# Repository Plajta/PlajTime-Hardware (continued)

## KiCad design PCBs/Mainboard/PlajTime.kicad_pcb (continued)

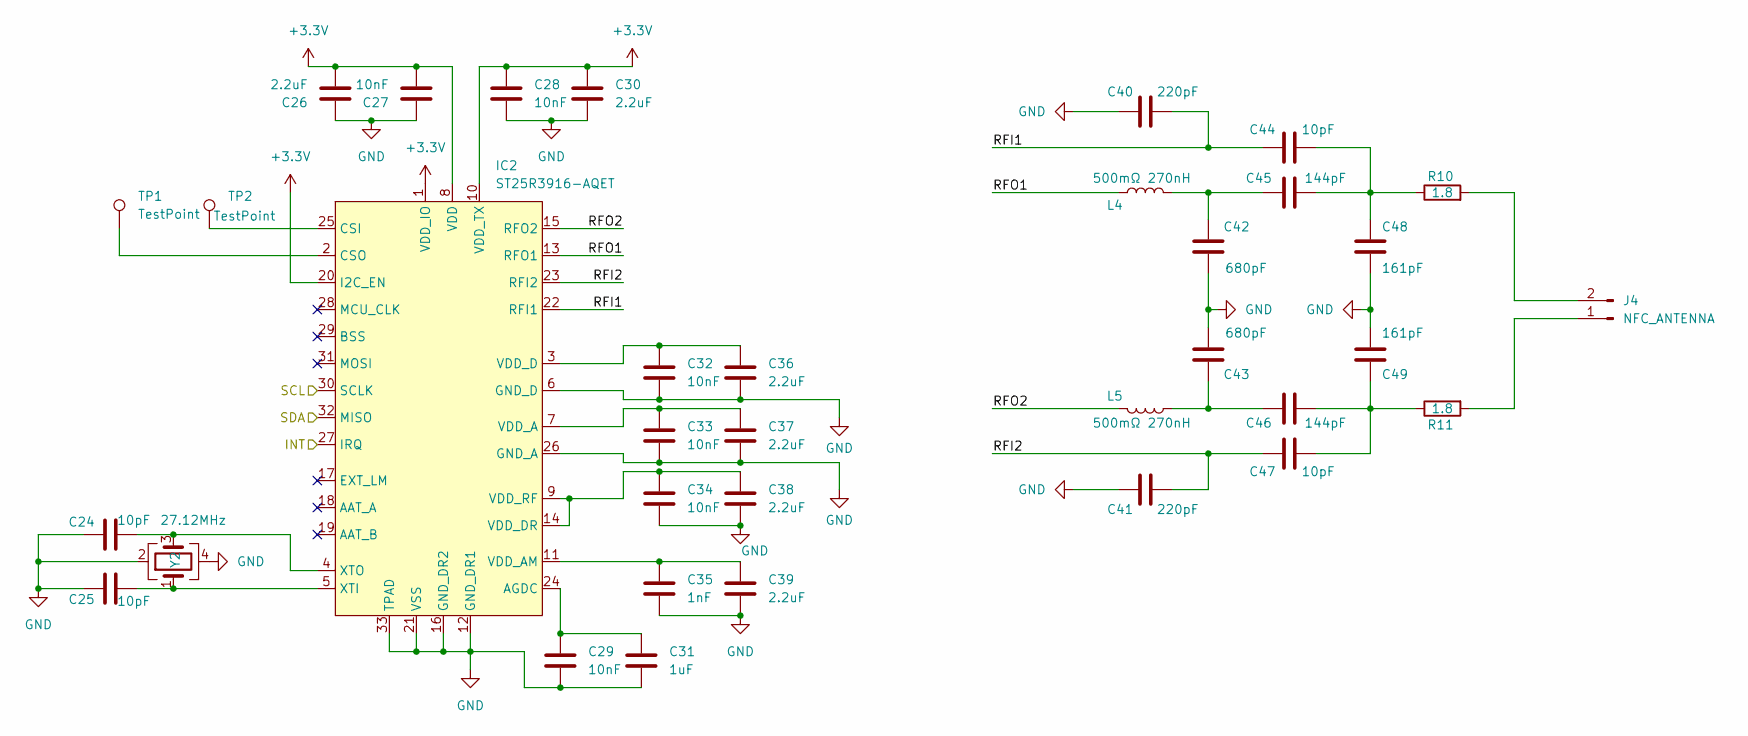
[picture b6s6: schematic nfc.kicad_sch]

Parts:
C24, C25, C44, C47: 10pF; C_0201_0603Metric
C26, C30, C36, C37, C38, C39: 2.2uF; C_0201_0603Metric
C27, C28, C29, C32, C33, C34: 10nF; C_0201_0603Metric
C31: 1uF; C_0201_0603Metric
C35: 1nF; C_0201_0603Metric
C40, C41: 220pF; C_0201_0603Metric
C42, C43: 680pF; C_0201_0603Metric
C45, C46: 144pF; C_0201_0603Metric
C48, C49: 161pF; C_0201_0603Metric
IC2: ST25R3916-AQET
J4: NFC_ANTENNA; PinHeader_1x02_P1.00mm_Vertical
L4, L5: 500mΩ 270nH; L_0603_1608Metric
R10, R11: 1.8; R_0201_0603Metric
TP1, TP2: TestPoint; TestPoint_Pad_D1.0mm
Y2: 27.12MHz; Oscillator_SMD_Abracon_ASCO-4Pin_1.6x1.2mm

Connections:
+3.3V: C26.2, C27.2, C28.1, C30.1, IC2.1 (VDD_IO), IC2.8 (VDD), IC2.10 (VDD_TX), IC2.20 (I2C_EN); also elsewhere on the board
/Display/SCL: IC2.30 (SCLK); also elsewhere on the board
/Display/SDA: IC2.32 (MISO); also elsewhere on the board
/NFC/RFI1: C40.2, C44.1, IC2.22 (RFI1)
/NFC/RFI2: C41.2, C47.1, IC2.23 (RFI2)
/NFC/RFO1: IC2.13 (RFO1), L4.1
/NFC/RFO2: IC2.15 (RFO2), L5.1
/NFC_INT: IC2.27 (IRQ); also elsewhere on the board
GND: C24.1, C25.2, C26.1, C27.1, C28.2, C29.2, C30.2, C31.2, C32.2, C33.2, C34.2, C35.2, C36.2, C37.2, C38.2, C39.2, C40.1, C41.1, C42.2, C43.2, C48.2, C49.2, IC2.6 (GND_D), IC2.12 (GND_DR1), IC2.16 (GND_DR2), IC2.21 (VSS), IC2.26 (GND_A), IC2.33 (TPAD), Y2.2, Y2.4; also elsewhere on the board
unnamed: C42.1, C45.1, L4.2
unnamed: C43.1, C46.1, L5.2
unnamed: C44.2, C45.2, C48.1, R10.1
unnamed: C46.2, C47.2, C49.1, R11.1
unnamed: C29.1, C31.1, IC2.24 (AGDC)
unnamed: IC2.25 (CSI), TP2.1
unnamed: IC2.2 (CSO), TP1.1
unnamed: C33.1, C37.1, IC2.7 (VDD_A)
unnamed: C35.1, C39.1, IC2.11 (VDD_AM)
unnamed: C32.1, C36.1, IC2.3 (VDD_D)
unnamed: C34.1, C38.1, IC2.9 (VDD_RF), IC2.14 (VDD_DR)
unnamed: C25.1, IC2.5 (XTI), Y2.1
unnamed: C24.2, IC2.4 (XTO), Y2.3
unnamed: J4.1, R11.2
unnamed: J4.2, R10.2

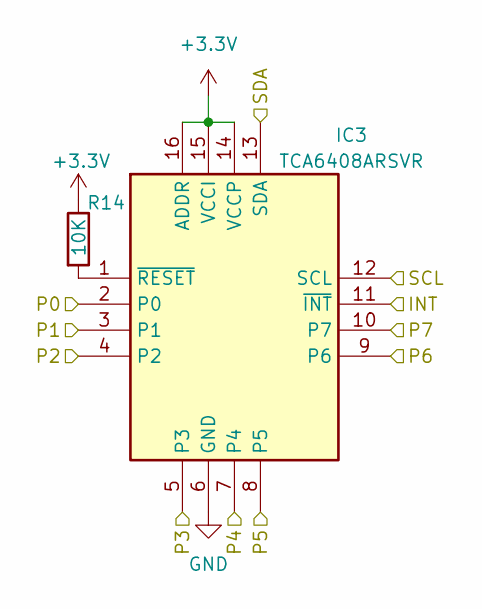
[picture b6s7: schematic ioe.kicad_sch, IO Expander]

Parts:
IC3: TCA6408ARSVR; QFN40P180X260X55-16N; Mouser Part Number 595-TCA6408ARSVR
R14: 10K; R_0201_0603Metric

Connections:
+3.3V: IC3.14 (VCCP), IC3.15 (VCCI), IC3.16 (ADDR), R14.1; also elsewhere on the board
/1V8_EN: IC3.5 (P3); also elsewhere on the board
/DP_RES: IC3.3 (P1); also elsewhere on the board
/Display/SCL: IC3.12 (SCL); also elsewhere on the board
/Display/SDA: IC3.13 (SDA); also elsewhere on the board
/ESP32_C3/INT2: IC3.11 (~INT); also elsewhere on the board
/IMU_INT: IC3.2 (P0); also elsewhere on the board
/LVL_SHIFT_EN: IC3.8 (P5); also elsewhere on the board
/NFC_INT: IC3.4 (P2); also elsewhere on the board
/OXY_INT: IC3.7 (P4); also elsewhere on the board
/PIC_INT: IC3.10 (P7); also elsewhere on the board
/VIC_INT: IC3.9 (P6); also elsewhere on the board
GND: IC3.6 (GND); also elsewhere on the board
unnamed: IC3.1 (~RESET), R14.2

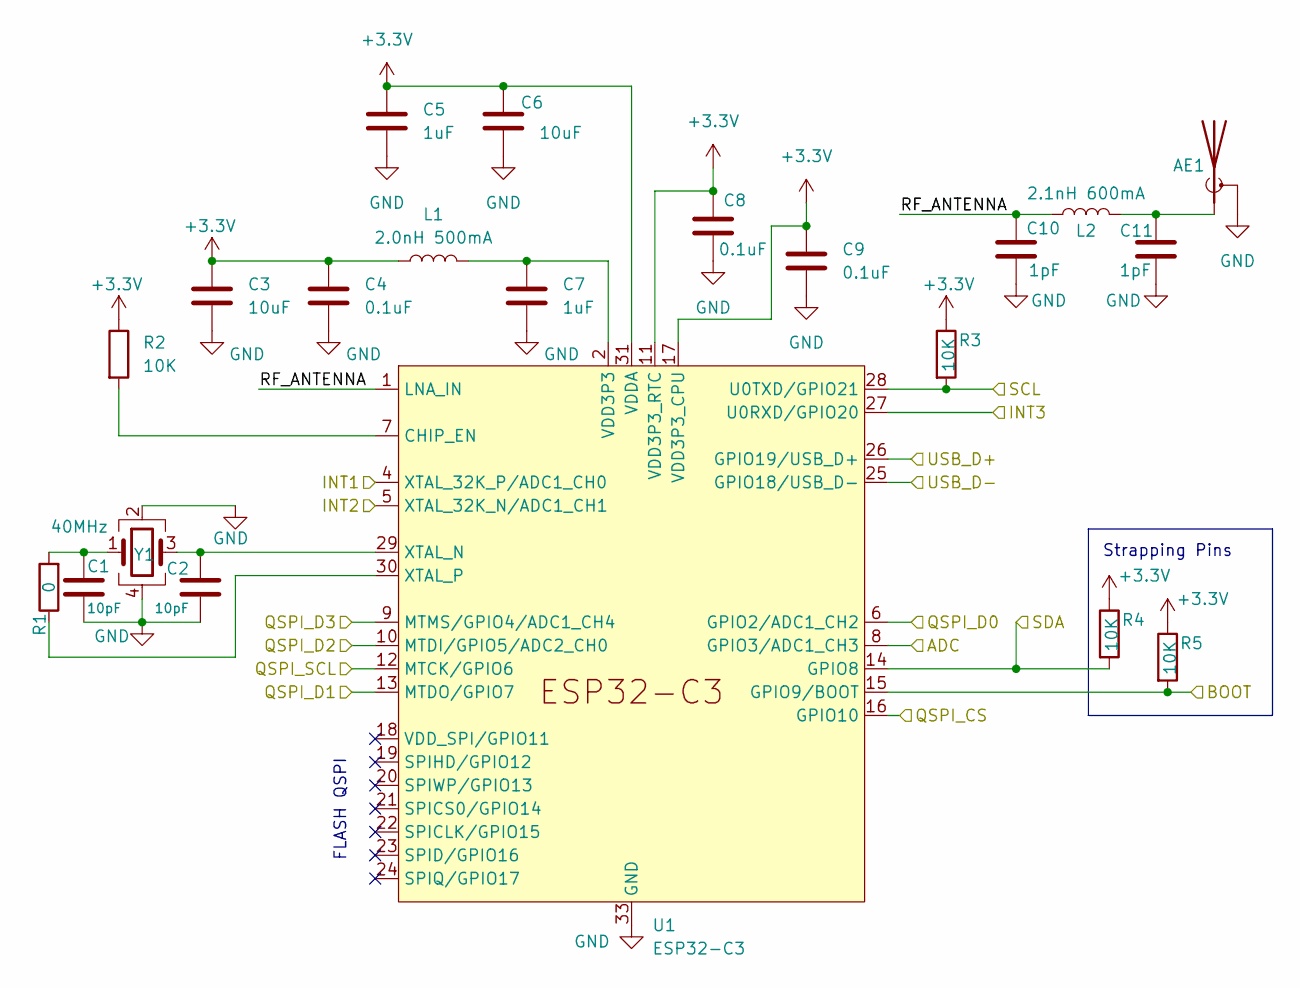
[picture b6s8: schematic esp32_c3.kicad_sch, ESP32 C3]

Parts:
AE1: Antenna_Shield; PinHeader_1x02_P1.00mm_Vertical
C1, C2: 10pF; C_0201_0603Metric
C3, C6: 10uF; C_0402_1005Metric
C4, C8, C9: 0.1uF; C_0201_0603Metric
C5, C7: 1uF; C_0201_0603Metric
C10, C11: 1pF; C_0201_0603Metric
L1: 2.0nH 500mA; L_0201_0603Metric
L2: 2.1nH 600mA; L_0201_0603Metric
R1: 0; R_0201_0603Metric
R2, R3, R4, R5: 10K; R_0201_0603Metric
U1: ESP32-C3; QFN-32-1EP_5x5mm_P0.5mm_EP3.45x3.45mm
Y1: 40MHz; Oscillator_SMD_Abracon_ASCO-4Pin_1.6x1.2mm

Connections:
+3.3V: C3.1, C4.1, C5.1, C6.1, C8.1, C9.1, L1.1, R2.1, R3.1, R4.1, R5.1, U1.11 (VDD3P3_RTC), U1.17 (VDD3P3_CPU), U1.31 (VDDA), U1.32 (VDDA); also elsewhere on the board
/Display/QSPI_CS: U1.16 (GPIO10); also elsewhere on the board
/Display/QSPI_D0: U1.6 (GPIO2/ADC1_CH2); also elsewhere on the board
/Display/QSPI_D1: U1.13 (MTDO/GPIO7); also elsewhere on the board
/Display/QSPI_D2: U1.10 (MTDI/GPIO5/ADC2_CH0); also elsewhere on the board
/Display/QSPI_D3: U1.9 (MTMS/GPIO4/ADC1_CH4); also elsewhere on the board
/Display/QSPI_SCL: U1.12 (MTCK/GPIO6); also elsewhere on the board
/Display/SCL: R3.2, U1.28 (U0TXD/GPIO21); also elsewhere on the board
/Display/SDA: R4.2, U1.14 (GPIO8); also elsewhere on the board
/Display/TE: U1.27 (U0RXD/GPIO20); also elsewhere on the board
/Display/TP_INT: U1.4 (XTAL_32K_P/ADC1_CH0); also elsewhere on the board
/ESP32_C3/ADC: U1.8 (GPIO3/ADC1_CH3); also elsewhere on the board
/ESP32_C3/BOOT: R5.2, U1.15 (GPIO9/BOOT); also elsewhere on the board
/ESP32_C3/INT2: U1.5 (XTAL_32K_N/ADC1_CH1); also elsewhere on the board
/ESP32_C3/RF_ANTENNA: C10.1, L2.1, U1.1 (LNA_IN)
/ESP32_C3/USB_D+: U1.26 (GPIO19/USB_D+); also elsewhere on the board
/ESP32_C3/USB_D-: U1.25 (GPIO18/USB_D-); also elsewhere on the board
GND: AE1.2 (Shield), C1.2, C2.2, C3.2, C4.2, C5.2, C6.2, C7.2, C8.2, C9.2, C10.2, C11.2, U1.33 (GND), Y1.2, Y1.4; also elsewhere on the board
unnamed: AE1.1 (A), C11.1, L2.2
unnamed: C1.1, R1.2, Y1.1
unnamed: C7.1, L1.2, U1.2 (VDD3P3), U1.3 (VDD3P3)
unnamed: R2.2, U1.7 (CHIP_EN)
unnamed: C2.1, U1.29 (XTAL_N), Y1.3
unnamed: R1.1, U1.30 (XTAL_P)

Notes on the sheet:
Strapping Pins
FLASH QSPI

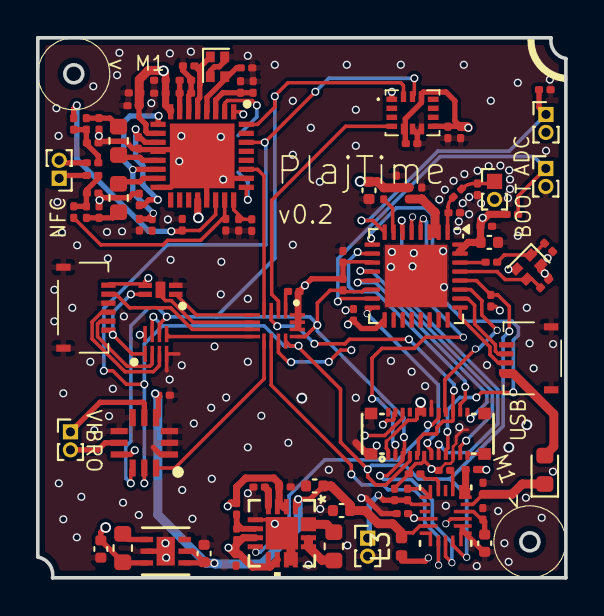
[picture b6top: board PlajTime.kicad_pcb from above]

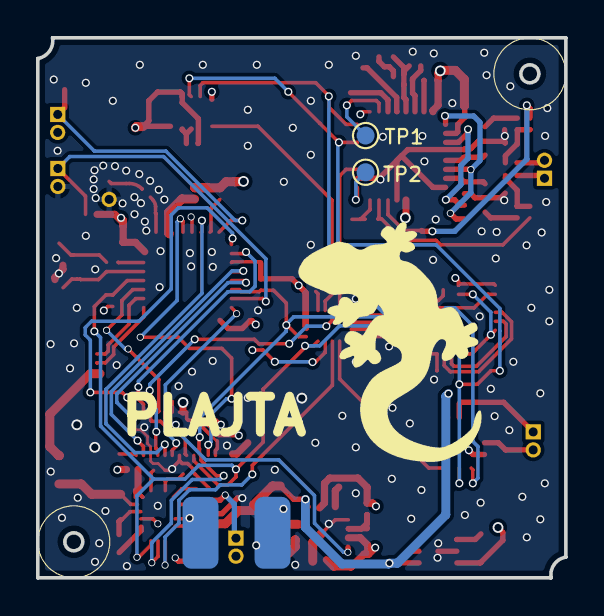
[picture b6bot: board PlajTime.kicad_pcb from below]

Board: 4 copper layers, 29.3 x 30.0 mm, 100 parts (3 on the bottom side), 76 nets.

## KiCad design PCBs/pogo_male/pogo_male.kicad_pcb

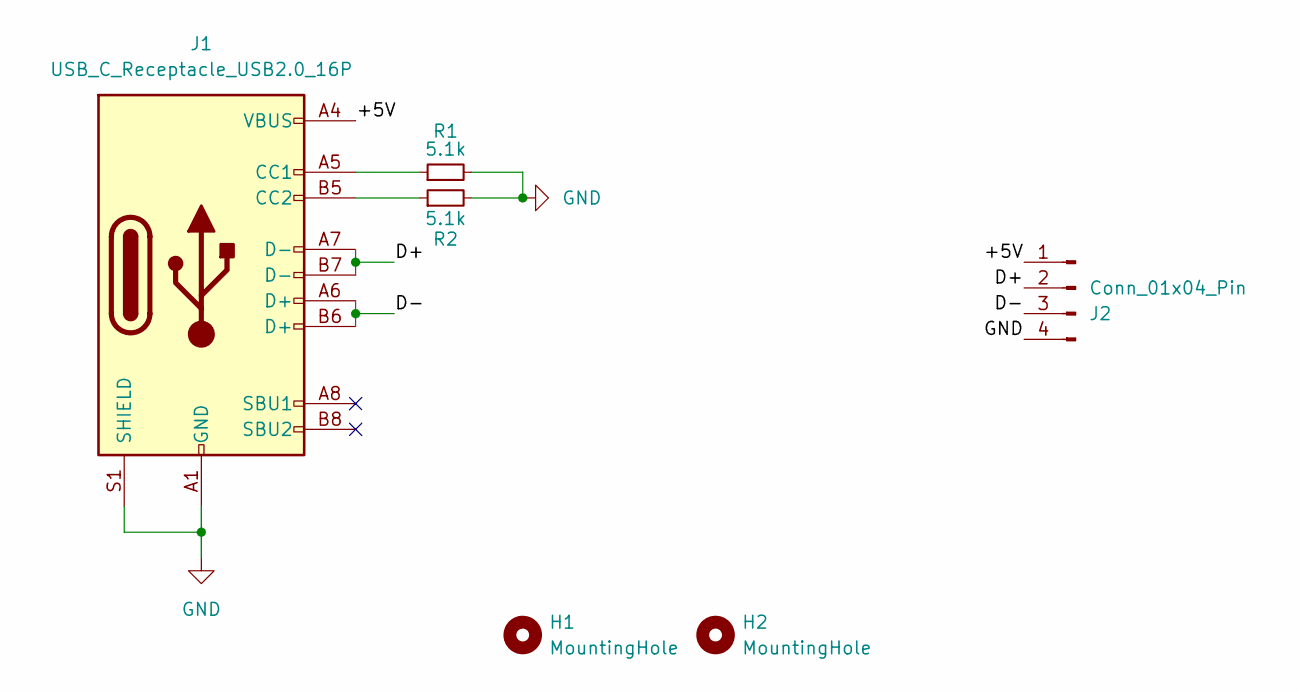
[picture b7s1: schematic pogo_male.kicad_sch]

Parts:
H1, H2: MountingHole; MountingHole_1.2mm_M1
J1: USB_C_Receptacle_USB2.0_16P; USB_C_Receptacle_G-Switch_GT-USB-7010ASV
J2: Conn_01x04_Pin; PinHeader_1x04_P2.54mm_Vertical
R1, R2: 5.1k; R_0402_1005Metric

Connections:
/+5V: J1.A4 (VBUS), J1.A9 (VBUS), J1.B4 (VBUS), J1.B9 (VBUS), J2.1
/D+: J1.A7 (D-), J1.B7 (D-), J2.2
/D-: J1.A6 (D+), J1.B6 (D+), J2.3
GND: J1.A1 (GND), J1.A12 (GND), J1.B1 (GND), J1.B12 (GND), J1.S1 (SHIELD), J2.4, R1.2, R2.2
unnamed: J1.A5 (CC1), R1.1
unnamed: J1.B5 (CC2), R2.1

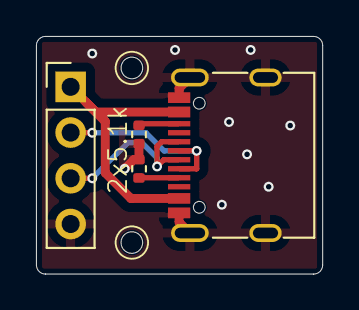
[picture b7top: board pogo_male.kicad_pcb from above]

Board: 2 copper layers, 15.9 x 13.2 mm, 6 parts (0 on the bottom side), 6 nets.

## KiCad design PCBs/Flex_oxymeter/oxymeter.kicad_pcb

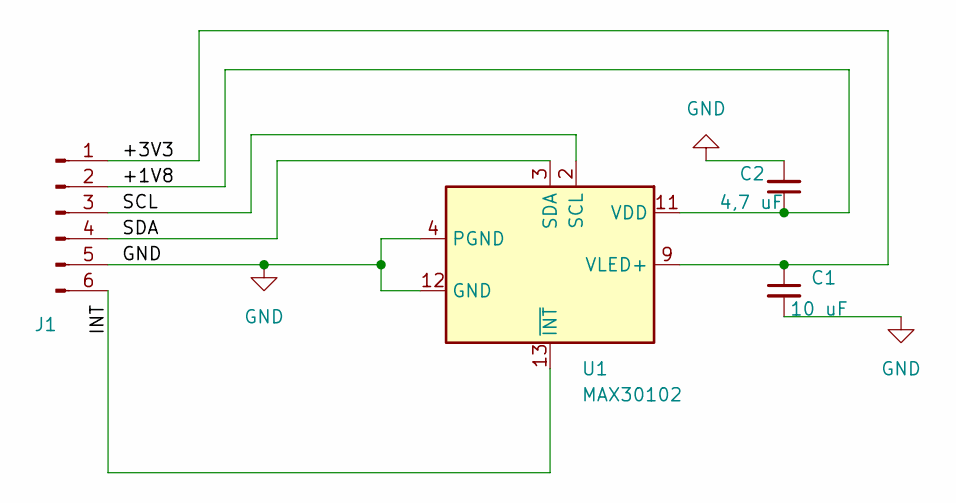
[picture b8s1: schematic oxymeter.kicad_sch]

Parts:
C1: 10 uF; C_0201_0603Metric
C2: 4,7 uF; C_0201_0603Metric
J1: Conn_01x06_Pin; edge_01x06
U1: MAX30102; Maxim_MAX30102

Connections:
/+1V8: C2.1, J1.2, U1.11 (VDD)
/+3V3: C1.1, J1.1, U1.9 (VLED+), U1.10 (VLED+)
/INT: J1.6, U1.13 (~INT)
/SCL: J1.3, U1.2 (SCL)
/SDA: J1.4, U1.3 (SDA)
GND: C1.2, C2.2, J1.5, U1.4 (PGND), U1.12 (GND)

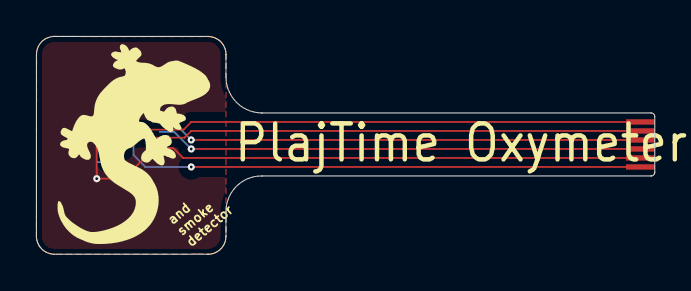
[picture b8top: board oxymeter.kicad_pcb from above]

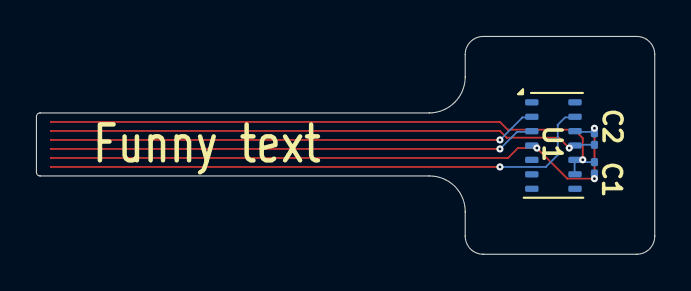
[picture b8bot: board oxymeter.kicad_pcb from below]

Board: 2 copper layers, 34.3 x 12.1 mm, 4 parts (3 on the bottom side), 6 nets.

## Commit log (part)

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2024-08-22 added watch enclosure
2024-08-22 collors yeah nice
2024-08-24 A lot of work has been done! PCB some schematic and 3D
2024-08-29 au bolest
2024-09-02 Some 3d changes
2024-11-22 Reorganize PCB directory Fix .gitignores
2024-11-24 Designed shassis for watch
2024-11-24 added 3mf files to print
2024-12-01 Add Kicad files for Oxymeter flex PCB It is NOT compatible with Mainboard v0.2 since it hasn't yet been updated.
2024-12-01 Add Kicad files for female pogo flex PCB
2024-12-01 Add WIP Kicad files for male pogo PCB
2024-12-02 OHHH Cool shassis and a lot of broken code
2024-12-03 some fixes, touch is a bit faster but a bit laggy
2025-01-07 Fixed vulnerability in 3Ds
2025-01-07 Added more space for display pogo flex pcb and button
2025-01-07 Changed old 3mf to new one
2025-01-09 home is here! brothers
2025-01-10 Cleaning work space
2025-01-15 Added STLs and some minor changes in model
2025-01-17 Minor changes in 3D model
2025-01-30 Update schematic info and add plot in PDF
2025-01-30 Update schematic info and add PDFs for auxiliary boards
2025-02-09 Minor fix in chassis
2025-02-25 Added no turn off display after inactivity
2025-03-05 Added ablity to configure with menuconfig
2025-04-15 Transfered Model to Freecad 1.0.0
2025-04-22 Update the female magnetic Pogopin connector
    Update to KiCAD 9.0
    Add a differential skew to make the differential tracks ACTUALLY the same length (even to it doesn't matter at ESP's speed)
2025-04-24 Fix schematic title
    Also update to KiCAD 9
2025-09-19 Add LICENSE-CC-BY-SA
2025-09-19 Add a README.md
2025-10-30 Squished prototype v0.3 archive
2025-10-30 Clean repo for next prototype
2025-10-30 3D: Add model to show required fitting space
2026-01-26 3D is now has its sizes, PCB has almost done schematic and started work on layout
2026-02-06 Some layout is done
2026-02-08 Final?
2026-02-09 Some small changes
2026-02-09 Add and modify labels
    Modify mainly text thickness
2026-02-09 Move text around a bit
    for future fruity changes
2026-02-09 Add a nice PCB graphic, tweak text
    Add a nice citrus inspired PCB graphic for the bottom side of PlajTime v0.4
2026-02-09 Some small final touches
2026-02-17 Final Main PCB version
2026-03-01 Fixes for bug that I found for now, added right models
2026-03-07 feat: Add new KiCad project for battery flexible PCB, updating main, auxiliary, and 3D models.
2026-03-10 Almost done AUX Board
2026-03-11 Done with battery FPCB
2026-03-11 Add graphics for AUX FPCB
    Redo asset README a bit and move assets
    Remove the pogo pins from the solderpaste layer
2026-03-11 Fix dielectric materials on BAT and AUX
    Add dimensions to BAT and fix it's thickness
2026-03-11 Fix names for AUX graphics
2026-03-11 Update AUX board's top graphic
2026-03-14 Added stiffener for BAT FPCB
2026-03-14 Done with AUX board
2026-03-14 Add graphics for BAT FPCB
    Preapplied to the KiCAD files
2026-03-14 Revise and update FPCB graphics
2026-03-14 Add 3D models for all chips on AUX board
2026-03-14 Changes in 3D model
2026-03-14 Add 3D models for AUX board and connectors
2026-03-15 Fix graphics on both FPCBs
    Change how text is put on paths
    Remove country of origin text
2026-03-15 Update export paths and fills on FPCBs
2026-03-16 Added git ignore for production
2026-03-16 Changed to bigger vias
2026-03-17 Edited via sizes
2026-03-25 All production fixes
2026-04-30 Formal remarks, added usb pins holder to model
